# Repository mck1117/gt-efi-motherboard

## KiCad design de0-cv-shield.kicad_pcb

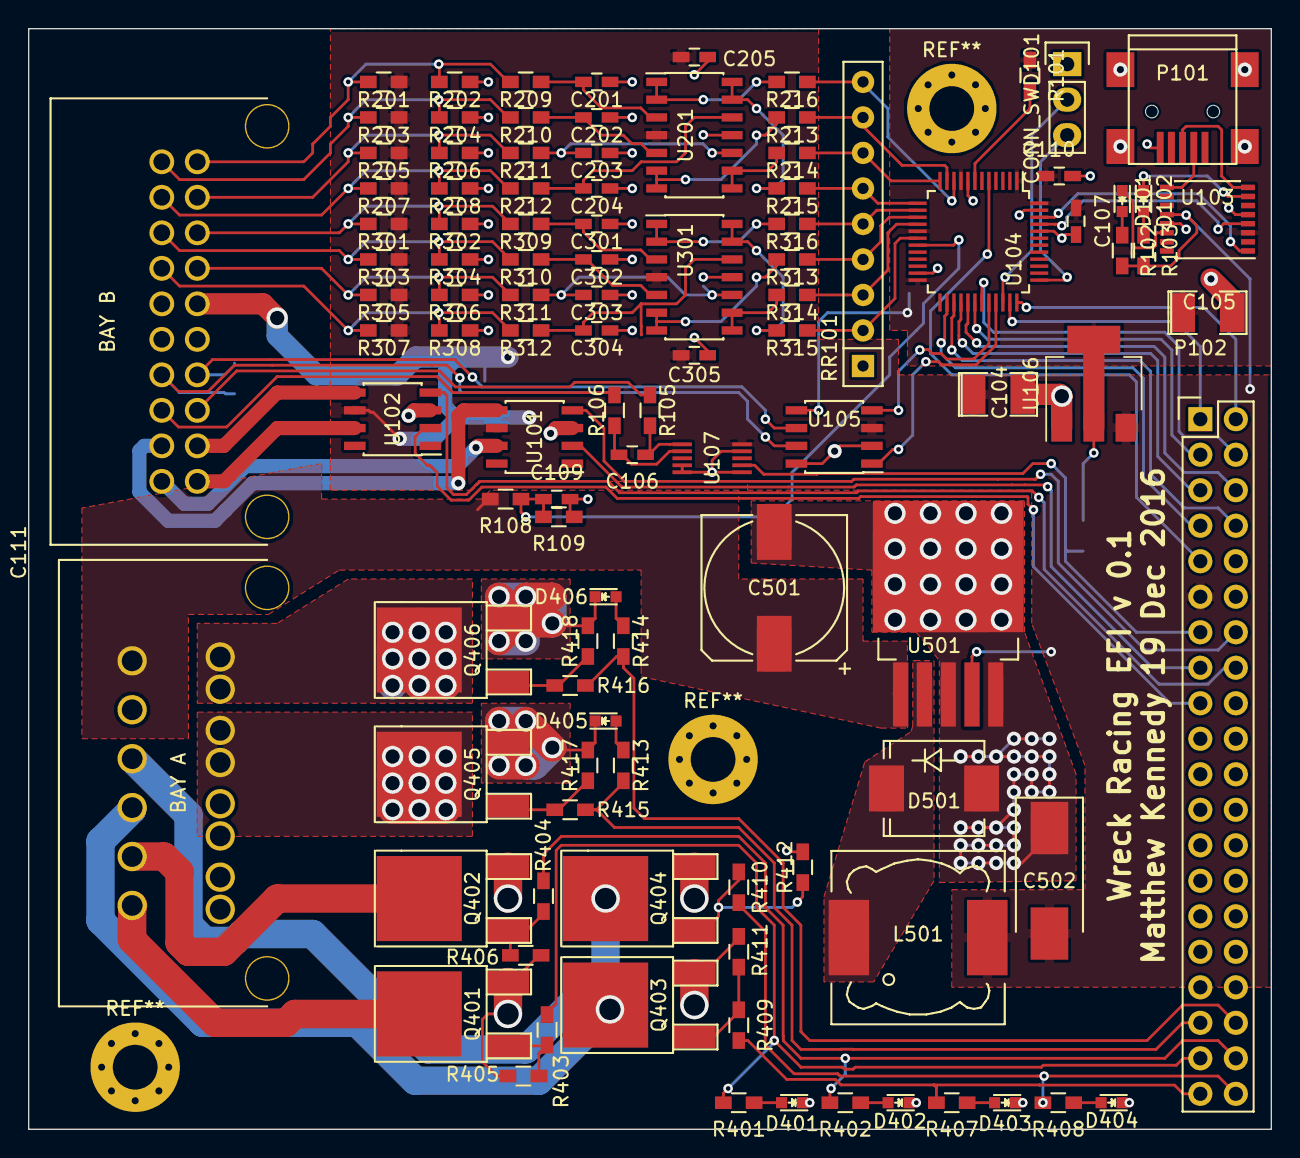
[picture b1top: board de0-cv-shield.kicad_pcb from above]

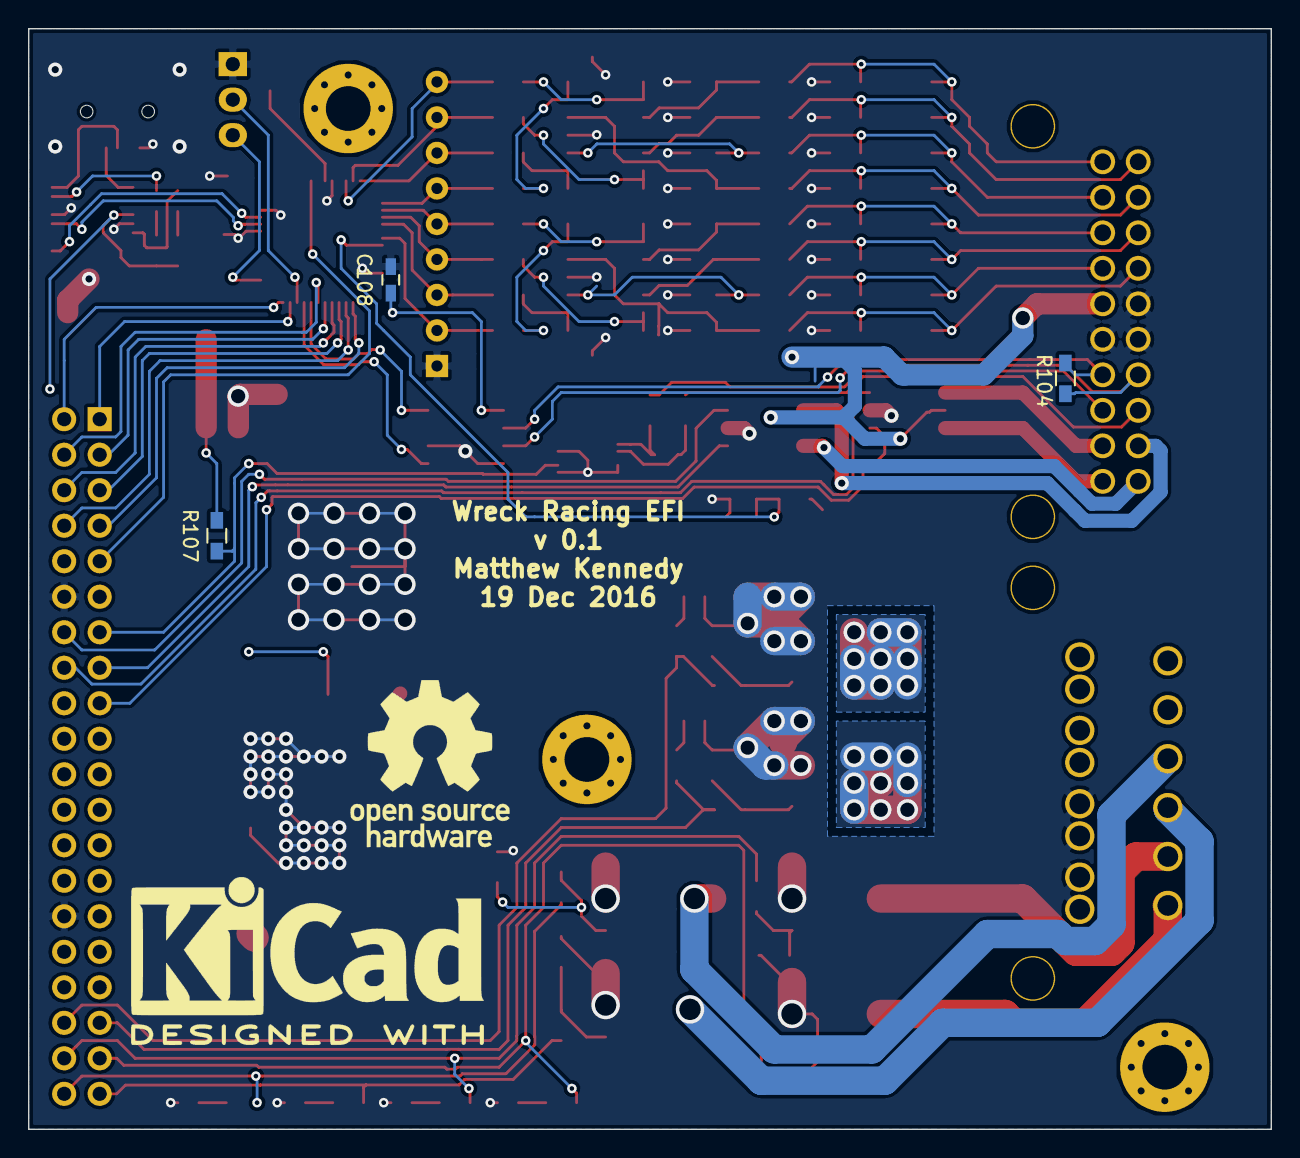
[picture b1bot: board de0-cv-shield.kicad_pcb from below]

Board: 2 copper layers, 88.9 x 78.7 mm, 109 parts (3 on the bottom side), 99 nets.

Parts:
C104: CP; SMD-1210_Pol
C105: 22uF; SMD-1210_Pol
C106: 1nF; C_0603_HandSoldering
C107, C108: .1uF; C_0603_HandSoldering
C109, C201, C202, C203, C204, C301, C302, C303, C304: 0.01uF; C_0603_HandSoldering
C110: 4.7uF; C_0603_HandSoldering
C111: MOLEX_34703_2012; MOLEX_34707-2012
C205, C305: 0.1uF; C_0603_HandSoldering
C501: 330uF; c_elec_10x10
C502: 220uF; Tantalum_Case-D_EIA-7343-31_Hand
CONN_SWD101: CONN_01X03; Pin_Header_Straight_1x03
D101, D102, D401, D402, D403, D404, D405, D406: LED; LED_0603
D501: D_Schottky; SMC_Standard
L501: 38uH; Choke_SMD_12x12mm_h6mm
P101: USB_OTG; USB_Mini-B
P102: CONN_02X20; Pin_Header_Straight_2x20
Q401, Q402, Q403, Q404, Q405, Q406: IRF540N; TO-252-2Lead
R101, R105, R106, R107, R109, R209, R210, R211, R212, R309, R310, R311, R312: 10k; R_0603_HandSoldering
R102, R103, R401, R402, R407, R408, R413, R414: 1k; R_0603_HandSoldering
R104: 120; R_0603_HandSoldering
R108: 100k; R_0603_HandSoldering
R201, R202, R203, R204, R205, R206, R207, R208, R301, R302, R303, R304, R305, R306, R307, R308: R; R_0603_HandSoldering
R213, R214, R215, R216, R313, R314, R315, R316: 1500; R_0603_HandSoldering
R403, R404, R409, R410, R415, R416: 20; R_0603_HandSoldering
R405, R406, R411, R412, R417, R418: 20k; R_0603_HandSoldering
RR101: RR8; Resistor_Array_SIP9
U101, U102: ISL89410; SOIC-8_3.9x4.9mm_Pitch1.27mm
U103: FT230XS; SSOP-16_4.4x5.2mm_Pitch0.65mm
U104: STM32F373CCTx; LQFP-48_7x7mm_Pitch0.5mm
U105: MCP2562-E/SN; SOIC-8_3.9x4.9mm_Pitch1.27mm
U106: LD1117S33TR; SOT-223
U107: MAX9924; uMAX-10
U201, U301: LM324; SOIC-14_3.9x8.7mm_Pitch1.27mm
U501: LM2576xx; TO-263-5Lead

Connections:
+3V3: C105.1, C107.1, C108.1, C110.1, R101.1, R107.2, U103.3, U104.1, U104.9, U104.17, U104.24, U104.48, U105.5, U106.2
+5V: C104.1, C111.26, C205.1, C305.1, C502.2, L501.2, P102.11, R102.2, R103.2, R201.2, R203.2, R205.2, R207.2, R301.2, R303.2, R305.2, R307.2, U101.6, U102.6, U103.12, U105.3, U106.3, U107.10, U201.4, U301.4, U501.4
+12V: C111.6, C501.1, R108.2, U501.1
AIN0: C111.30, R201.1, R202.2, R209.2
AIN1: C111.20, R203.1, R204.2, R210.2
AIN2: C111.29, R205.1, R206.2, R211.2
AIN3: C111.19, R207.1, R208.2, R212.2
AIN4: C111.28, R301.1, R302.2, R309.2
AIN5: C111.18, R303.1, R304.2, R310.2
AIN6: C111.27, R305.1, R306.2, R311.2
AIN7: C111.17, R307.1, R308.2, R312.2
CANH: C111.14, R104.2, U105.7
CANL: C111.24, R104.1, U105.6
CAN_RX: U104.32, U105.4
CAN_TX: U104.33, U105.1
FPGA_G1: P102.2, U104.36
FPGA_G2: P102.1, U104.35
FPGA_G3: P102.4, U104.31
FPGA_G4: P102.3, U104.30
FPGA_G5: P102.6, U104.29
FPGA_MCU_CLK: P102.9, U104.5
FPGA_MISO: P102.7, U104.26
FPGA_MOSI: P102.8, U104.27
FPGA_SCK: P102.5, U104.28
GND: C104.2, C105.2, C107.2, C108.2, C109.2, C110.2, C111.7, C111.8, C111.15, C111.16, C111.25, C201.2, C202.2, C203.2, C204.2, C205.2, C301.2, C302.2, C303.2, C304.2, C305.2, C501.2, C502.1, CONN_SWD101.1, D401.1, D402.1, D403.1, D404.1, D405.1, D406.1, D501.2, P101.5, P101.6, P102.12, P102.30, Q401.3, Q402.3, Q403.3, Q404.3, Q405.3, Q406.3, R109.1, R202.1, R204.1, R206.1, R208.1, R302.1, R304.1, R306.1, R308.1, R405.2, R406.2, R411.2, R412.2, R417.2, R418.2, RR101.1, U101.3, U102.3, U103.5, U103.13, U104.8, U104.23, U104.44, U104.47, U105.2, U105.8, U106.1, U107.4, U107.5, U107.6, U107.9, U201.11, U301.11, U501.3, U501.5
IGN_A_IN: P102.15, U101.2
IGN_A_OUT: C111.11, U101.7
IGN_B_IN: P102.14, U101.4
IGN_B_OUT: C111.12, U101.5
IGN_C_IN: P102.17, U102.2
IGN_C_OUT: C111.21, U102.7
IGN_D_IN: P102.16, U102.4
IGN_D_OUT: C111.22, U102.5
INJ_A_IN: P102.35, R413.2, R415.2
INJ_B_IN: P102.36, R414.2, R416.2
unnamed: C106.1, R105.1, U107.1
unnamed: C106.2, R106.1, U107.2
unnamed: C109.1, R108.1, R109.2, U104.19
unnamed: C201.1, R209.1, U201.3
unnamed: C202.1, R210.1, U201.5
unnamed: C203.1, R211.1, U201.10
unnamed: C204.1, R212.1, U201.12
unnamed: C301.1, R309.1, U301.3
unnamed: C302.1, R310.1, U301.5
unnamed: C303.1, R311.1, U301.10
unnamed: C304.1, R312.1, U301.12
unnamed: CONN_SWD101.2, U104.34
unnamed: CONN_SWD101.3, U104.37
unnamed: D101.1, U103.14
unnamed: D101.2, R102.1
unnamed: D102.1, U103.7
unnamed: D102.2, R103.1
unnamed: D401.2, R401.1
unnamed: D402.2, R402.1
unnamed: D403.2, R407.1
unnamed: D404.2, R408.1
unnamed: D405.2, R413.1
unnamed: D406.2, R414.1
unnamed: D501.1, L501.1, U501.2
unnamed: P101.2, U103.9
unnamed: P101.3, U103.8
unnamed: Q401.1, R403.1, R405.1
unnamed: Q402.1, R404.1, R406.1
unnamed: Q403.1, R409.1, R411.1
unnamed: Q404.1, R410.1, R412.1
unnamed: Q405.1, R415.1, R417.1
unnamed: Q406.1, R416.1, R418.1
unnamed: R101.2, U104.7
unnamed: R213.1, U201.6, U201.7
unnamed: R214.1, U201.8, U201.9
unnamed: R215.1, U201.13, U201.14
unnamed: R216.1, U201.1, U201.2
unnamed: R313.1, U301.6, U301.7
unnamed: R314.1, U301.8, U301.9
unnamed: R315.1, U301.13, U301.14
unnamed: R316.1, U301.1, U301.2
VR+: C111.23, R105.2
VR-: C111.13, R106.2
VRIN: P102.13, R107.1, U107.7
a0: R216.2, RR101.9, U104.10
a1: R213.2, RR101.8, U104.11
a2: R214.2, RR101.7, U104.12
a3: R215.2, RR101.6, U104.13
a4: R316.2, RR101.5, U104.14
a5: R313.2, RR101.4, U104.15
a6: R314.2, RR101.3, U104.16
a7: R315.2, RR101.2, U104.18
ftdi_rx: U103.4, U104.45
ftdi_tx: U103.1, U104.46
inj_a: C111.9, Q405.2
inj_b: C111.10, Q406.2
ls_1: P102.37, R401.2, R403.2
ls_2: P102.38, R402.2, R404.2
ls_3: P102.39, R407.2, R409.2
ls_4: P102.40, R408.2, R410.2
ls_out_1: C111.1, Q401.2
ls_out_2: C111.2, Q402.2
ls_out_3: C111.3, Q403.2
ls_out_4: C111.4, Q404.2

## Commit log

2016-12-20 Draft v0.1 mobo
2016-12-20 Fix wrong FTDI wiring, add silk board label
2016-12-20 Add top silk
2016-12-20 Add v0.1 fab gerbers
